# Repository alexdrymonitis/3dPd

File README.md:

# 3dPd

This repository hosts the code, schematics, and circuit board designs made in Kicad, for a hardware digital modular synthesizer. The audio is programmed in Pure Data and the hardware control in the Arduino language.
This synthesizer is supposed to run on a Raspberry Pi 3 and a Teensy3.2. You're welcome to use any other hardware you like, but this specific hardware is supported and explained here.

## Note about the Arduino code

Go to the Arduino_code directory and read the README.txt file first. That should give you enough information about the Arduino code. Do that before you start reading the Pd patches.

## Note about the Pd patches

The heart of this project is the modular_synthesizer.pd patch. Open it and you'll see some other abstractions in there. Go into the [pd modules] sub-patch and look inside.
Each module must have its own abstraction. There are some tutorial module abstractions which show you how to build your own. Open them and read them carefully.

There's also a debug.pd patch which helps with debugging by showing input from the Teensy and printing various message concerning module connections and LED states.

### Dependencies

This project uses the following external libraries:  
zexy  
comport  
iemmatrix  
iemguts  
ggee  
list-abs  
tabreceive_mult~  

The first five libraries are being installed with "apt-get" and the last two are installed through Deken (In Pd got to Help -> Find externals and type these two names -one at a time-, the highlighted version(s) is good for your system).

Pd-0.47.0 or higher is required.

## General note

I'll upload a wiki with instructions for creating the hardware of a module and the whole system. It's in my TODO list, which will hopefully happen in the near future.
You can watch a demo video of the synthesizer here https://www.youtube.com/watch?v=HD13bDPyBWA

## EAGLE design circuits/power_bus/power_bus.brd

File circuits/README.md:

# Circuit designs, schematics, and gerber files directory

This README file provides only very basic information about the circuits. I'm planning on releasing a wiki on how to build hardware modules in the next few days.

## Generic note about this directory

In this directory you'll find all the circuits used in this modular synthesizer. It's six circuits in total, each in its own directory. They have been designed in Kicad and all the necessary files are here. Each directory includes a README file which states which extra built-in libraries have been used. The ones I have made especially for these circuits are not mentioned in the README since their directories (library/ and .pretty/) are included here. The directories also include the gerber files for sending them to a manufacturer, plus a .png file for each side (in case of double-sided boards) in case you want to DIY etch it, and a .pdf with the schematic.

If you've never used Kicad before and want to modify any of the circuits, I recommend to read some of the tutorials provided from Kicad's website. This tutorial was very useful for me http://kicad-pcb.org/help/documentation/#_getting_started. If you just want to have them manufactured, you can send the gerber files straight to a manufacturer.

## Note about the circuits

### Parts

There's a parts list in every circuit directory with all the parts of that circuit. Where I thought it was necessary, I provide a link to the datasheet of that part. Parts are identified by their annotation from the schematic. Consult the board design (Pcbnew) to make sure which part goes where.

### Orientation of parts

The orientation of the ICs on the "module_generic_top_board" is not defined by the shape of the footprint part but by the pin numbering. If you're not sure, open Pcbnew, go to View -> 3D Viewer and there you can see the notches of the ICs which indicate their orientation.
The orientation of the IDC connectors can be defined by the pin numbering. On an actual IDC connector, you can see a small arrow at the left side of the notch. This arrow indicates that the left-most pin on the side of the notch, is pin number 1.

### Concerning manufacturing

The boards "module_generic_top_board" and "module_generic_bottom_board" are needed for every module. I would suggest to order these from a manufacturer instead of etching them your self many times. The "module_specific_board" and "module_specific_board"2 are just examples of how you can connect your parts to the generic boards (this will be analyzed in the upcoming wiki). There are two of those because I wanted to provide both orientations for the potentiometers, because of the knobs one can find (they are D-shaped knobs, so orientation is rather important). You can order few of these as well, since it is designed in such a way that can host many different layouts.

The "power_bus", "power_distributor", and "teensy_motherboard" are designed as single-side circuit boards (with the "teensy_motherboard" using three jumpers, the "power_bus" only one, and the "power_distributor" none) so that it's easier to etch them yourself. You'll need only one per board (unless you want to build more than 16 modules, then you'll need a second "power_bus", explained in the upcoming wiki), so ordering those from a manufacturer might not work out.

Eacn board has a .pdf file which you can print for DIY etching, either with toner transfer or with photo-resistant boards. The "module_generic_top_board", "module_generic_bottom_board", and "module_specific_board" have two .pdf, one for each side, while the rest three have only one .pdf file.

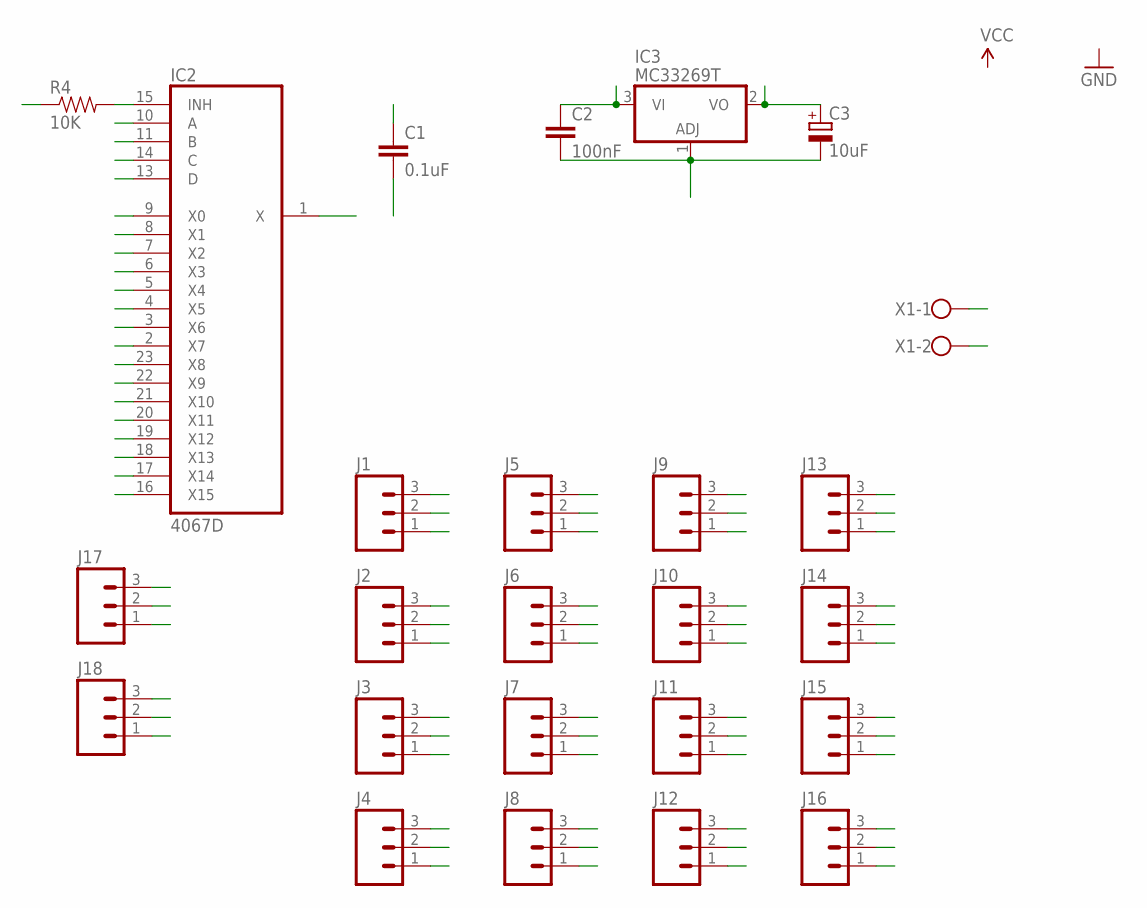
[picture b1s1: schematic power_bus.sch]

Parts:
C1: 0.1uF; CAP-PTH-SMALLEZ
C2: 100nF; CAP-PTH-SMALLEZ
C3: 10uF; E5-4
IC2: 4067D; SO24W
IC3: MC33269T; TO220V
J1, J2, J3, J4, J5, J6, J7, J8, J9, J10, J11, J12, J13, J14, J15, J16: M03JST-PTH-VERT; JST-3-PTH-VERT
J17, J18: M03PTH; 1X03
R4: 10K; AXIAL-0.3
X1: W237-102

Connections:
MUX0: IC2.9 (X0), J1.3
MUX1: IC2.8 (X1), J2.3
MUX2: IC2.7 (X2), J3.3
MUX3: IC2.6 (X3), J4.3
MUX4: IC2.5 (X4), J5.3
MUX5: IC2.4 (X5), J6.3
MUX6: IC2.3 (X6), J7.3
MUX7: IC2.2 (X7), J8.3
MUX8: IC2.23 (X8), J9.3
MUX9: IC2.22 (X9), J10.3
MUX10: IC2.21 (X10), J11.3
MUX11: IC2.20 (X11), J12.3
MUX12: IC2.19 (X12), J13.3
MUX13: IC2.18 (X13), J14.3
MUX14: IC2.17 (X14), J15.3
MUX15: IC2.16 (X15), J16.3
MUX_A: IC2.10 (A), J17.1
MUX_B: IC2.11 (B), J18.1
MUX_C: IC2.14 (C), J18.3
MUX_D: IC2.13 (D), J17.3
MUX_X: IC2.1 (X), J17.2
unnamed: IC2.15 (INH), R4.P$2 (2)
VDD: C1.1, C3.+, IC2.24 (VDD), IC3.2 (VO), J1.1, J2.1, J3.1, J4.1, J5.1, J6.1, J7.1, J8.1, J9.1, J10.1, J11.1, J12.1, J13.1, J14.1, J15.1, J16.1
VOLTAGE: C2.1, IC3.3 (VI), X1.1
VSS: C1.2, C2.2, C3.-, IC2.12 (VSS), IC3.1 (ADJ), J1.2, J2.2, J3.2, J4.2, J5.2, J6.2, J7.2, J8.2, J9.2, J10.2, J11.2, J12.2, J13.2, J14.2, J15.2, J16.2, J18.2, R4.P$1 (1), X1.2

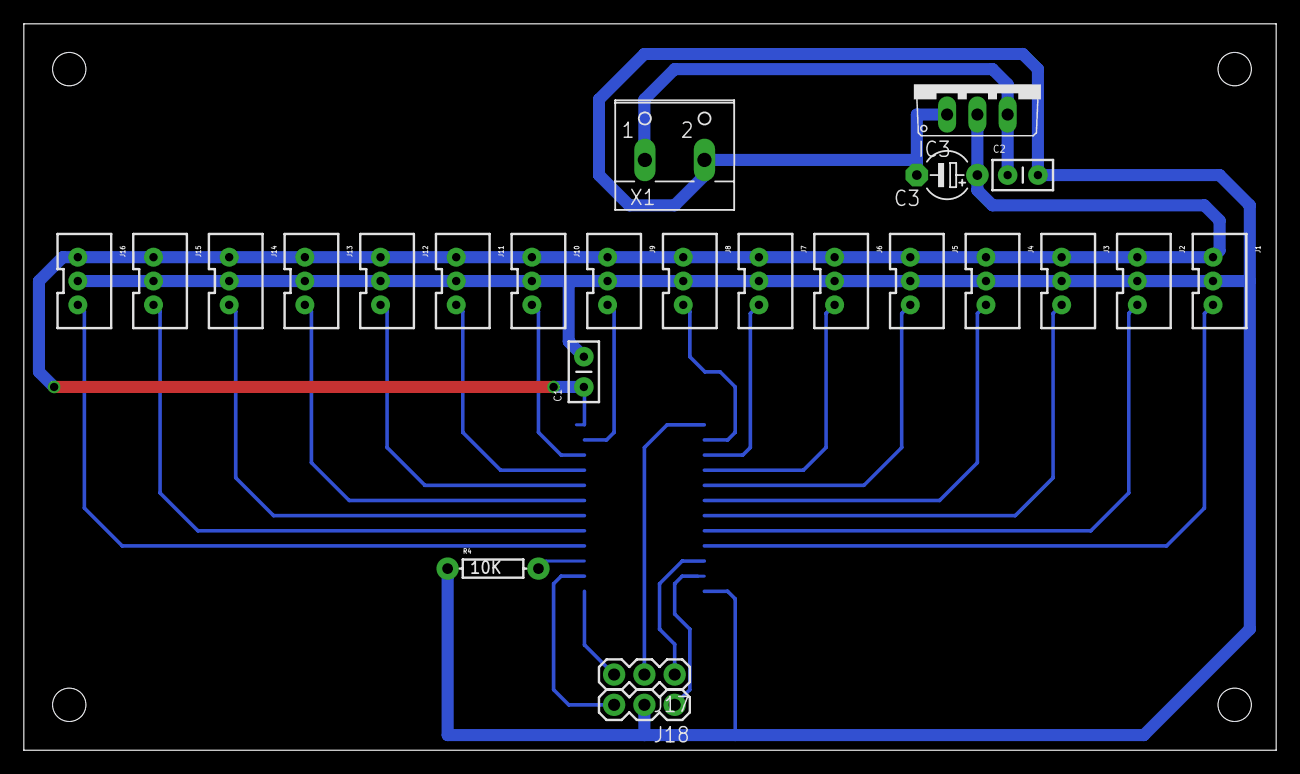
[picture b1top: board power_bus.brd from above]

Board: 2 copper layers, 105.1 x 61.0 mm, 25 parts (1 on the bottom side), 25 nets.

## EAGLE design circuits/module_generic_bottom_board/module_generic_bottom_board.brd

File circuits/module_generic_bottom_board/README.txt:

This circuit contains the switches schematic parts library from /usr/share/kicak/library

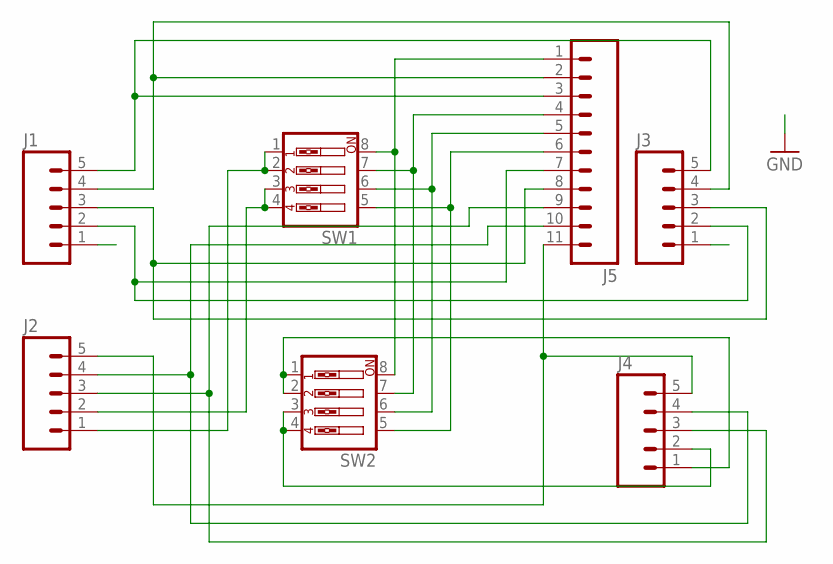
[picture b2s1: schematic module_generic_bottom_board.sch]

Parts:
J1, J2, J3, J4: M05PTH; 1X05
J5: M11PTH; 1X11
SW1, SW2: SW_DIP-4; EDG-04

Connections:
GND: J1.1, J3.1
unnamed: J2.3, J4.3, J5.9
unnamed: J2.4, J4.4, J5.10
unnamed: J2.5, J4.5, J5.11
unnamed: J2.1, SW1.1, SW1.2
unnamed: J5.1, SW1.8, SW2.8
unnamed: J5.4, SW1.7, SW2.7
unnamed: J5.5, SW1.6, SW2.6
unnamed: J5.6, SW1.5, SW2.5
unnamed: J1.3, J3.3, J5.8
unnamed: J1.2, J3.2, J5.7
unnamed: J4.1, SW2.1, SW2.2
unnamed: J1.4, J3.4, J5.2
unnamed: J4.2, SW2.3, SW2.4
unnamed: J2.2, SW1.3, SW1.4
unnamed: J1.5, J3.5, J5.3

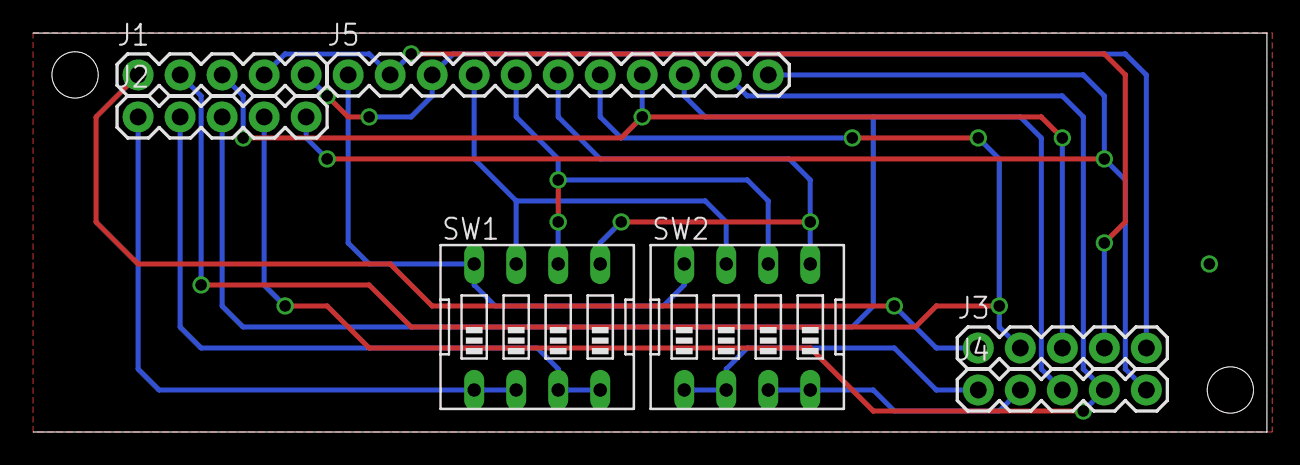
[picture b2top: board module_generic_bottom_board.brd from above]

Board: 2 copper layers, 74.6 x 24.1 mm, 7 parts (0 on the bottom side), 16 nets.

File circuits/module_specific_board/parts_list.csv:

Reference, Value, Footprint, Datasheet
P6,CONN_01X02,Header Male Straight 2-pin,
P3,CONN_01X08,Header Male Straight 8-pin,
P4,CONN_01X08,Header Male Straight 8-pin,
P5,CONN_01X08,Header Male Straight 8-pin,
J1,Pot,ALPS Rotary Potentiometer RK09L114001T,http://www.alps.com/prod/info/E/HTML/Potentiometer/RotaryPot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
J2,Pot,ALPS Rotary Potentiometer RK09L114001T,http://www.alps.com/prod/info/E/HTML/Potentiometer/RotaryPot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
J3,Pot,ALPS Rotary Potentiometer RK09L114001T,http://www.alps.com/prod/info/E/HTML/Potentiometer/RotaryPot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
J4,Pot,ALPS Rotary Potentiometer RK09L114001T,http://www.alps.com/prod/info/E/HTML/Potentiometer/RotaryPot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

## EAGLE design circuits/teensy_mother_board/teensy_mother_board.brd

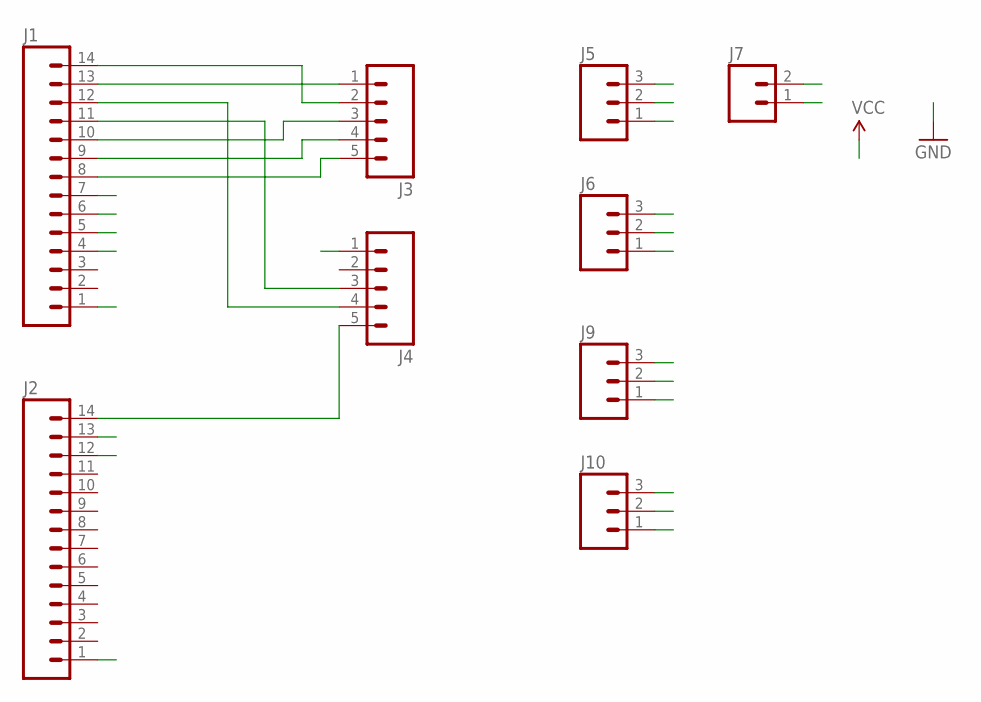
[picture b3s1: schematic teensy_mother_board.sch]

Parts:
J1, J2: M14; 1X14
J3, J4: M05PTH; 1X05
J5, J6, J9, J10: M03PTH; 1X03
J7: M02JST-PTH-VERT; JST-2-PTH-VERT

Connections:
GND: J1.1, J4.1, J6.2, J7.1, J10.2
IN_SER: J1.14, J3.2
MASTER_MUX1_IN: J2.13, J5.2
MASTER_MUX2_IN: J2.12, J9.2
MASTER_MUX_A: J1.7, J5.1, J9.1
MASTER_MUX_B: J1.6, J6.1, J10.1
MASTER_MUX_C: J1.5, J6.3, J10.3
MASTER_MUX_D: J1.4, J5.3, J9.3
OUT_SER: J1.13, J3.1
SCK_CLK: J2.14, J4.5
SH_LD: J1.11, J4.3
SLAVE_MUX_A: J1.10, J3.3
SLAVE_MUX_B: J1.9, J3.4
SLAVE_MUX_C: J1.8, J3.5
SS: J1.12, J4.4
VCC: J2.1, J7.2

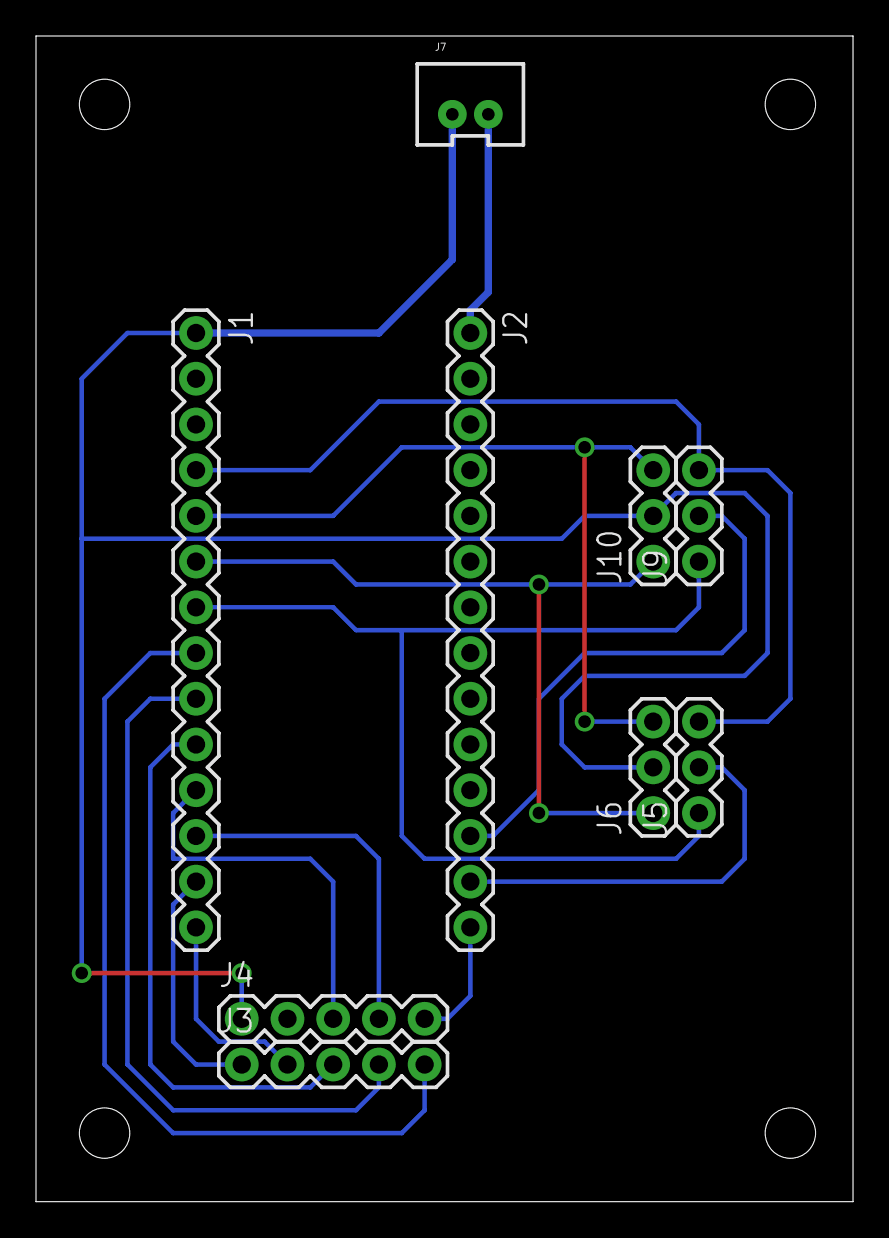
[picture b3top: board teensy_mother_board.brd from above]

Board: 2 copper layers, 45.4 x 64.8 mm, 9 parts (0 on the bottom side), 16 nets.

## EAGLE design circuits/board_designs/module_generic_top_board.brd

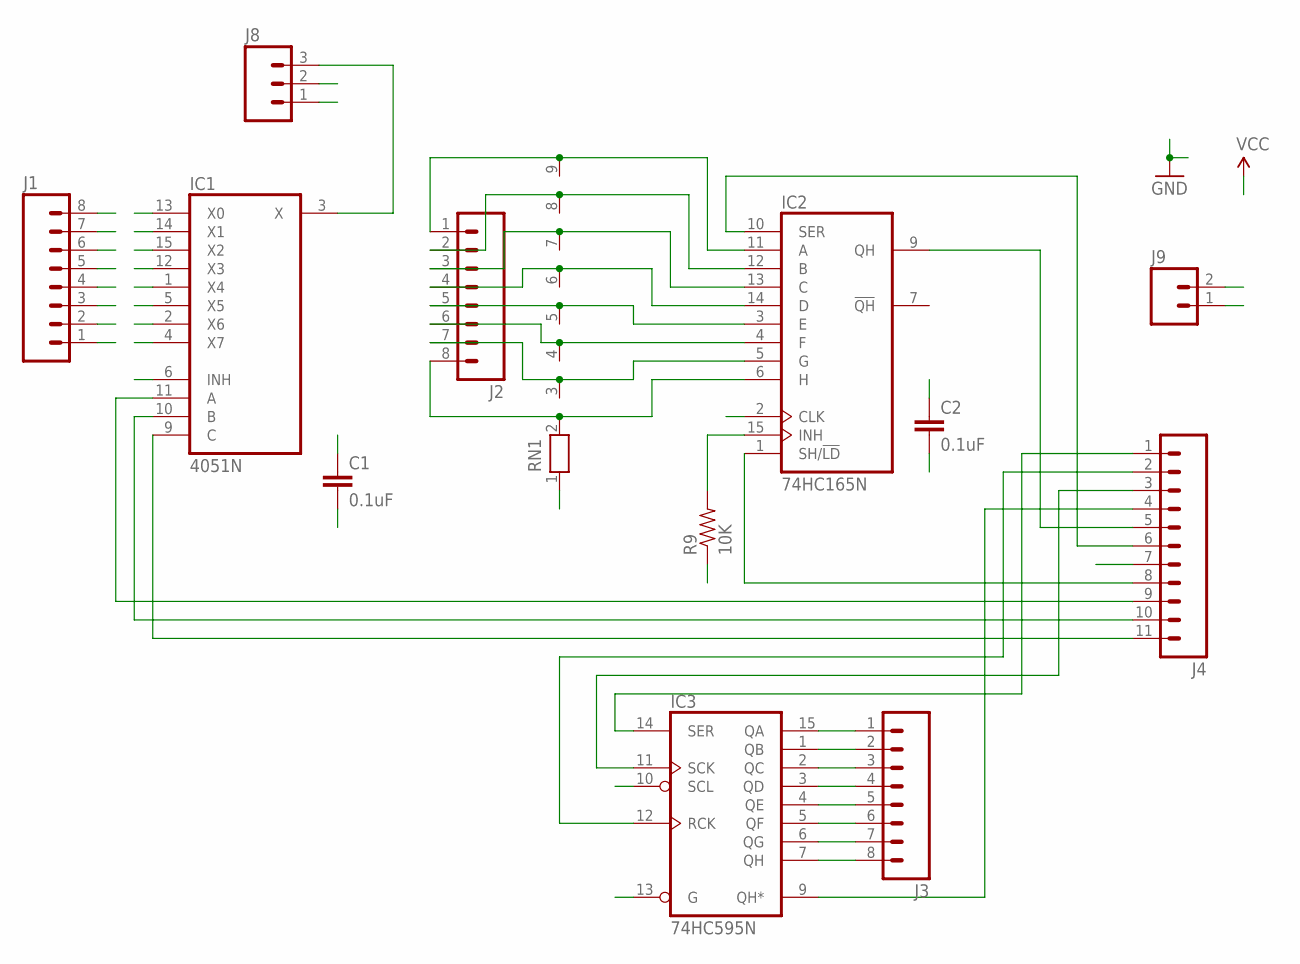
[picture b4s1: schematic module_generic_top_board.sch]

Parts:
C1, C2: 0.1uF; CAP-PTH-SMALLEZ
IC1: 4051N; DIL16
IC2: 74HC165N; DIL16
IC3: 74HC595N; DIL16
J1, J2, J3: M08; 1X08_ROUND
J4: M11PTH; 1X11
J8: M03JST-PTH; JST-3-PTH
J9: M02PTH; 1X02
R9: 10K; AXIAL-0.1
RN1: RN08; RN-9

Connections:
GND: C1.2, C2.2, IC1.6 (INH), IC1.7 (VEE), IC1.8 (GND), IC2.8 (GND), IC3.8 (GND), IC3.13 (G), J8.2, J9.2, R9.P$1 (1), RN1.1
INH: IC2.15 (INH), J4.7, R9.P$2 (2)
MUX_X0: IC1.13 (X0), J1.1
MUX_X1: IC1.14 (X1), J1.2
MUX_X2: IC1.15 (X2), J1.3
MUX_X3: IC1.12 (X3), J1.4
MUX_X4: IC1.1 (X4), J1.5
MUX_X5: IC1.5 (X5), J1.6
MUX_X6: IC1.2 (X6), J1.7
MUX_X7: IC1.4 (X7), J1.8
unnamed: IC2.9 (QH), J4.5
unnamed: IC2.10 (SER), J4.6
unnamed: IC2.1 (SH/!LD), J4.8
unnamed: IC3.14 (SER), J4.1
unnamed: IC3.12 (RCK), J4.2
unnamed: IC2.11 (A), J2.1, RN1.9
unnamed: IC3.9 (QH*), J4.4
unnamed: IC1.9 (C), J4.11
unnamed: IC1.10 (B), J4.10
unnamed: IC1.11 (A), J4.9
unnamed: IC2.12 (B), J2.2, RN1.8
unnamed: IC2.13 (C), J2.3, RN1.7
unnamed: IC2.14 (D), J2.4, RN1.6
unnamed: IC2.3 (E), J2.5, RN1.5
unnamed: IC2.4 (F), J2.6, RN1.4
unnamed: IC2.5 (G), J2.7, RN1.3
unnamed: IC3.15 (QA), J3.1
unnamed: IC3.1 (QB), J3.2
unnamed: IC3.2 (QC), J3.3
unnamed: IC3.3 (QD), J3.4
unnamed: IC3.4 (QE), J3.5
unnamed: IC3.5 (QF), J3.6
unnamed: IC3.6 (QG), J3.7
unnamed: IC3.7 (QH), J3.8
unnamed: IC1.3 (X), J8.3
unnamed: IC2.6 (H), J2.8, RN1.2
SCK_CLK: IC2.2 (CLK), IC3.11 (SCK), J4.3
VCC: C1.1, C2.1, IC1.16 (VCC), IC2.16 (VCC), IC3.10 (SCL), IC3.16 (VCC), J8.1, J9.1

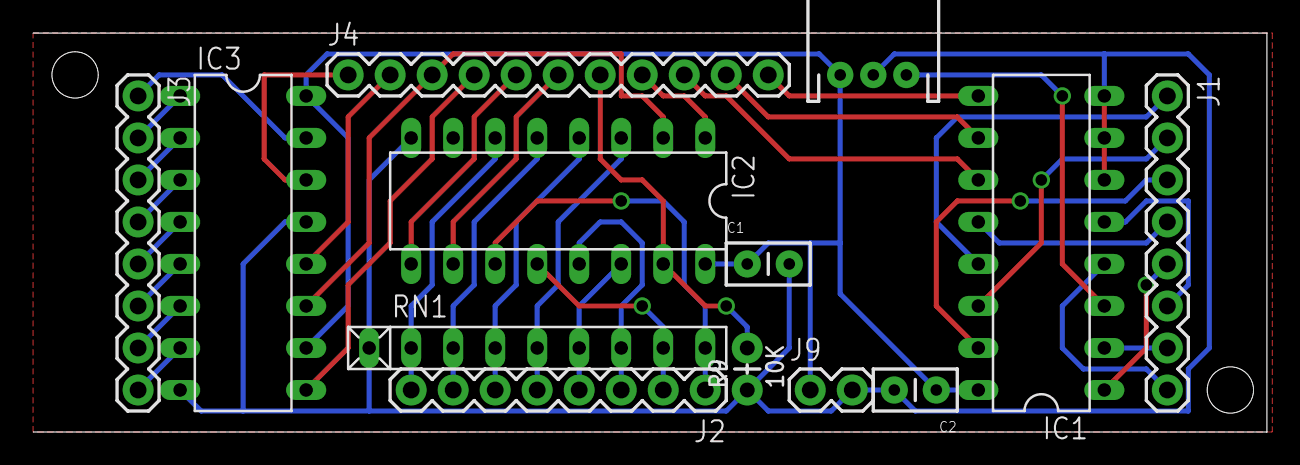
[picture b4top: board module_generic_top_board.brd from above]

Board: 2 copper layers, 74.6 x 24.1 mm, 13 parts (0 on the bottom side), 38 nets.

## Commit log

2016-08-11 minor corrections
2016-08-11 added circuit schematics and desings
2016-08-11 update abstractions
2016-08-11 update generic abstractions
2016-08-12 Update main patch
2016-08-12 Update [template_module~]
2016-08-12 Update [get_switches]
2016-08-12 Update [accumulate_connections]
2016-11-18 Update [arduino_data] abstraction
2016-11-18 Fixed smoothing issue in Arduino code
2016-11-18 Update analog smoothing
2017-06-11 added [module_input~]
2017-06-11 added [module_output~]
2017-06-11 added [input_state]
2017-06-11 added [output_state]
2017-07-01 Update Arduino sketches
2017-07-01 Update Pd Patches
2017-07-17 Include schematic .pdf files
2017-07-17 Update Arduino code
2017-07-19 Update envelope tutorial patch
2017-08-16 Update module specific board
2017-08-16 Replaced PNGs with PDFs
2017-08-16 Update PDF files
2017-09-01 Update patches and sketches
2017-09-01 removed alias module abstraction
2017-09-01 Update debug patch
2017-09-02 Update [module_data]
2017-09-02 Update [matrix_connections]
2017-09-03 Update 13-bug fix abstractions
2017-09-03 Update 13-bug fix code
2017-09-03 Update [arduino_data13]
2017-09-04 Update gerber files
2017-09-04 Update module_generic_bottom_board
2017-09-04 removed cache.lib file
2017-09-04 Update module template
2017-09-05 Update [module_input~]
2017-09-07 Update parts list
2017-09-10 Add [activity_ctl]
2017-09-10 Added tutorial_use_actinity_ctl.pd
2017-10-02 Update [module_output~]
2017-10-24 Update circuits
2017-10-24 Added Module Specific Board 2
2017-10-24 Update Module Generic Top Board

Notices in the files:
parts and their libraries:
SparkFun-Capacitors: Licensing: Creative Commons ShareAlike 4.0 International - https://creativecommons.org/licenses/by-sa/4.0
